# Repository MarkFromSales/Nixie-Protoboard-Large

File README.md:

# Nixie-Protoboard-Large Board
Protoboard for testing Nixie tube driving software development

I have a bunch of the new-old-stock K155ID1 chips that I found cheap on Amazon and eBay. I've been told NTE still makes the 74141 and found these links,

http://www.nteinc.com/specs/7400to7499/pdf/nte74141.pdf
http://dilp.netcomponents.com/cgi-bin/nteinc.asp?partnumber1=NTE74141

# Nixie Tube Tester Code
Learning to code for the Arduino for a Nixie tube project.
ATmega328 Driving SN74141 Nixie driver chip via pins A, B, C, & D

## Attributions and Thanks
- ATMega328 outside of Arduino Uno - https://dronebotworkshop.com/arduino-uno-atmega328/
- Multi-tasking the Arduino - https://learn.adafruit.com/multi-tasking-the-arduino-part-1?view=all

## Connections
```
ATMega328 Pin 28 (Analog 5 - I2C Clock) to MCP Pin 12
ATMega328 Pin 27 (Analog 4 - I2C Data)  to MCP Pin 13

MCP Pins #15, 16 and 17 are address selection (see below)
MCP Pin  9 to 5V
MCP Pin 10 to GND
MCP Pin 18 to 10K Resistor to 5V (reset pin, active low)
```

## MCP Addresses
```
addr 0 = A2 low,  A1 low,  A0 low  000
addr 1 = A2 low,  A1 low,  A0 high 001
addr 2 = A2 low,  A1 high, A0 low  010
addr 3 = A2 low,  A1 high, A0 high 011
addr 4 = A2 high, A1 low,  A0 low  100
addr 5 = A2 high, A1 low,  A0 high 101
addr 6 = A2 high, A1 high, A0 low  110
addr 7 = A2 high, A1 high, A0 high 111
```

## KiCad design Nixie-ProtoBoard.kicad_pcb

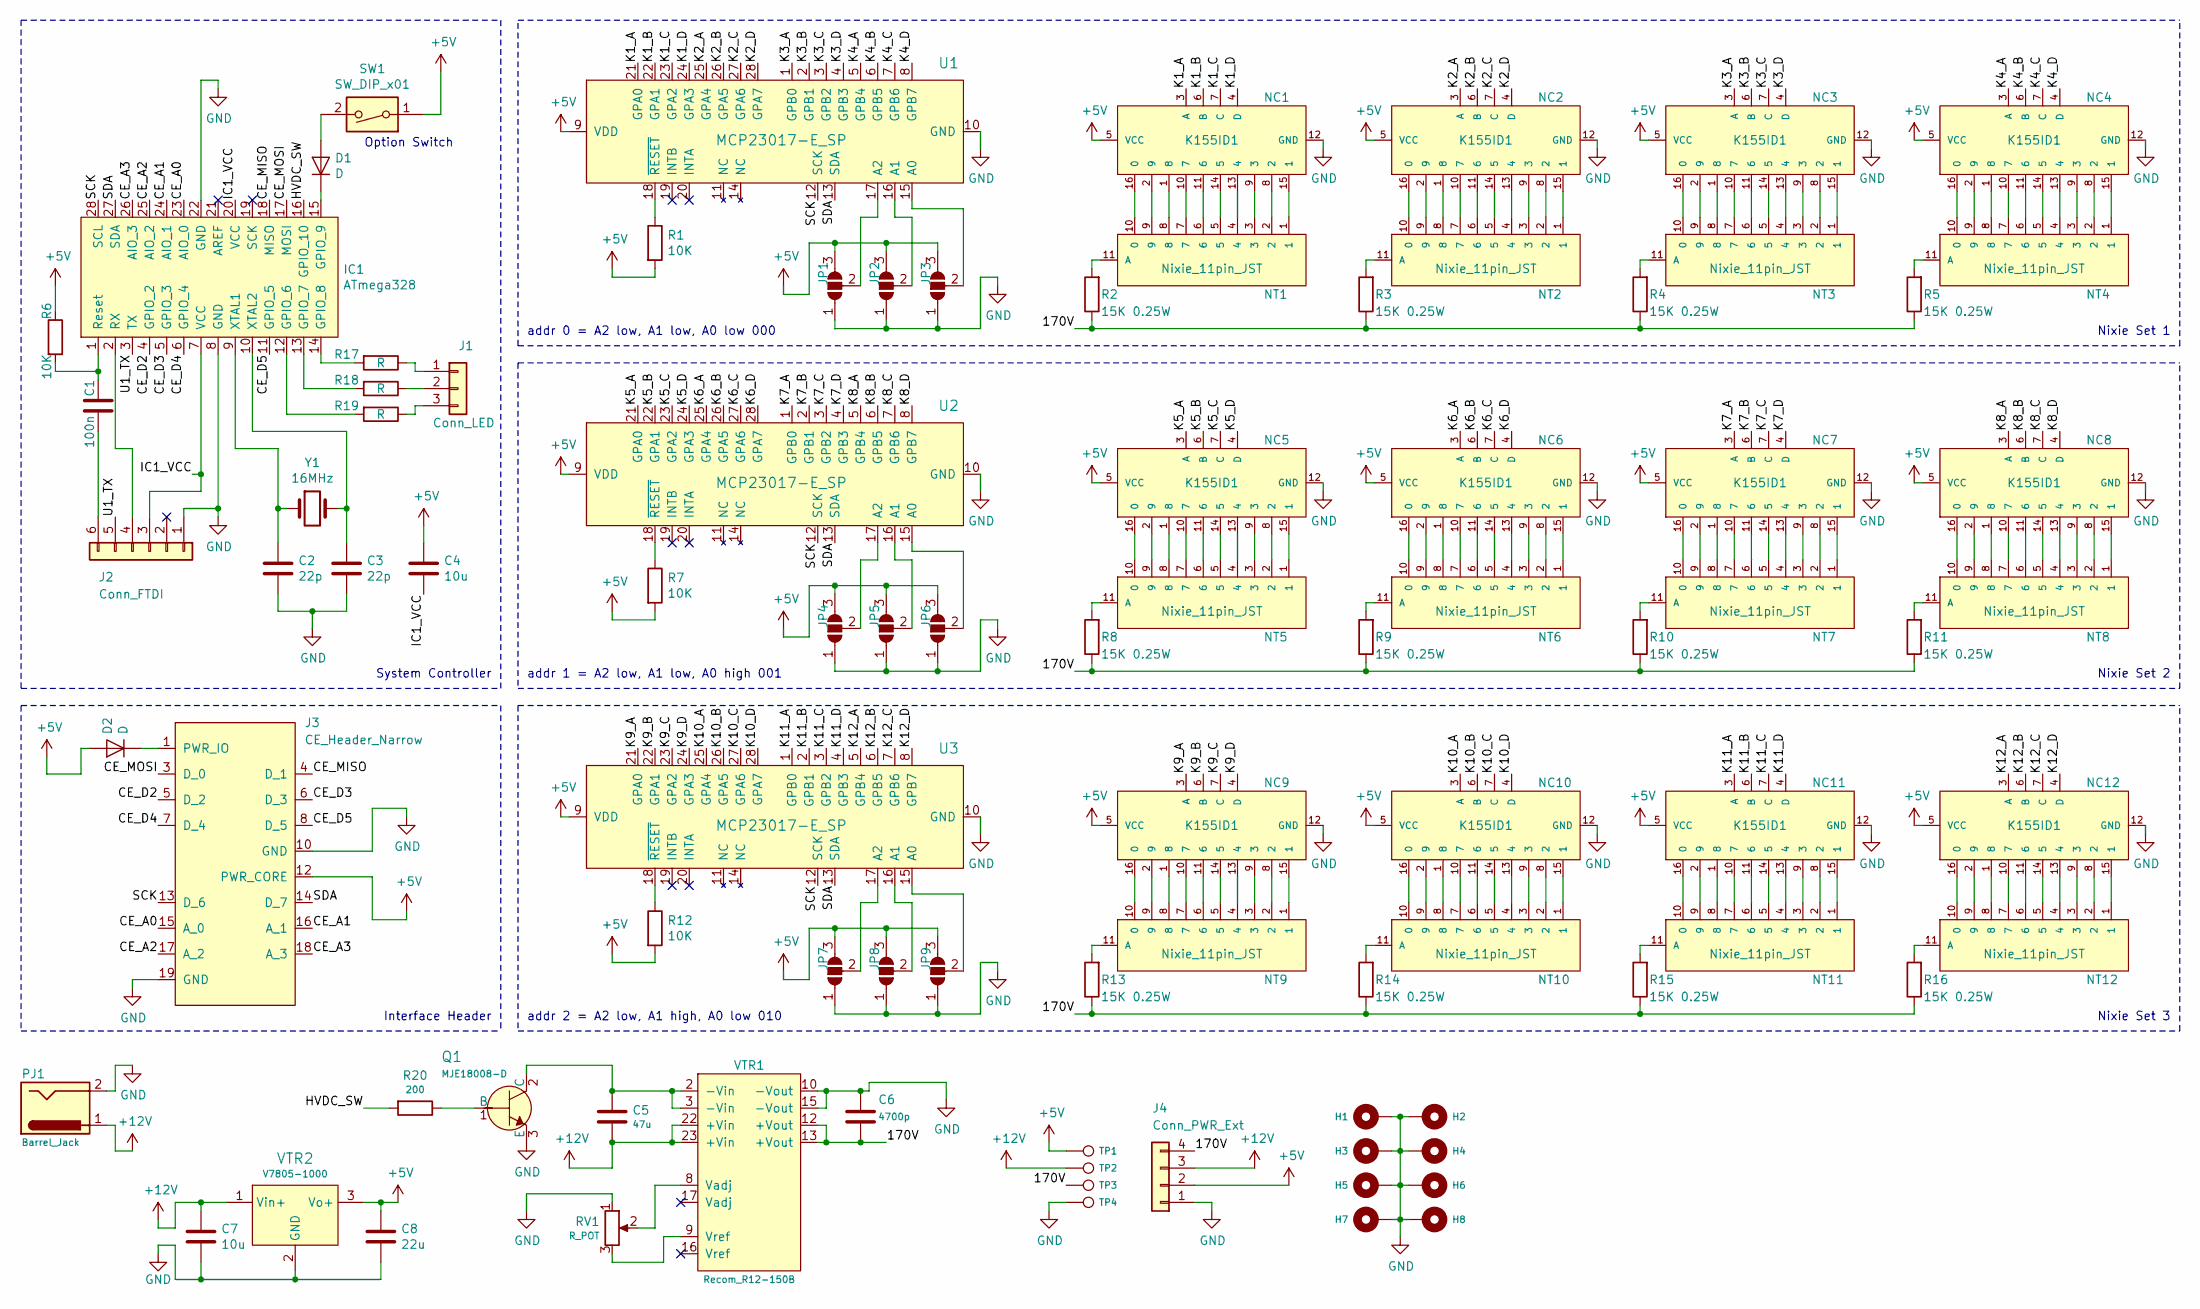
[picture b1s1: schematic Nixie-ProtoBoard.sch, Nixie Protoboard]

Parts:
C1: 100n; C_Disc_D10.5mm_W5.0mm_P7.50mm
C2, C3: 22p; C_0805_2012Metric_Pad1.15x1.40mm_HandSolder
C4, C7: 10u; C_0805_2012Metric_Pad1.15x1.40mm_HandSolder
C5: 47u; C_0805_2012Metric_Pad1.15x1.40mm_HandSolder
C6: 4700p; C_0805_2012Metric_Pad1.15x1.40mm_HandSolder
C8: 22u; CP_Radial_D5.0mm_P2.50mm
D1, D2: D; D_0805_2012Metric_Pad1.15x1.40mm_HandSolder
H1, H2, H3, H4, H5, H6, H7, H8: MountingHole_Pad; MountingHole_3.2mm_M3_Pad
IC1: ATmega328; DIP-28_W7.62mm_Socket
J1: Conn_LED; JST_XH_B03B-XH-A_1x03_P2.50mm_Vertical
J2: Conn_FTDI; PinHeader_1x06_P2.54mm_Vertical
J3: CE_Header_Narrow; PinHeader_2x10_P2.54mm_Vertical
J4: Conn_PWR_Ext; JST_VH_B4P-VH_1x04_P3.96mm_Vertical
JP1, JP2, JP3, JP4, JP5, JP6, JP7, JP8, JP9: SolderJumper_3_Open; SolderJumper-3_P1.3mm_Open_RoundedPad1.0x1.5mm_NumberLabels
NC1, NC2, NC3, NC4, NC5, NC6, NC7, NC8, NC9, NC10, NC11, NC12: K155ID1; DIP-16_W7.62mm_Socket
NT1, NT2, NT3, NT4, NT5, NT6, NT7, NT8, NT9, NT10, NT11, NT12: Nixie_11pin_JST; JST_XH_B11B-XH-A_1x11_P2.50mm_Vertical
PJ1: Barrel_Jack; BarrelJack_CUI_PJ-102AH_Horizontal
Q1: MJE18008-D; TO-220-3; MPN MJE15030G; Digi-Key_PN MJE15030GOS-ND
R1, R6, R7, R12: 10K; R_0805_2012Metric_Pad1.15x1.40mm_HandSolder
R2, R3, R4, R5, R8, R9, R10, R11, R13, R14, R15, R16: 15K 0.25W; R_0805_2012Metric_Pad1.15x1.40mm_HandSolder
R17, R18, R19: R; R_0805_2012Metric_Pad1.15x1.40mm_HandSolder
R20: 200; R_0805_2012Metric_Pad1.15x1.40mm_HandSolder
RV1: R_POT; Potentiometer_Vishay_43_Horizontal
SW1: SW_DIP_x01; PinHeader_1x02_P2.54mm_Vertical
TP1, TP2, TP3, TP4: TestPoint; TestPoint_Pad_D2.0mm
U1, U2, U3: MCP23017-E_SP; DIP-28_W7.62mm; MPN MCP23017-E/SP; Digi-Key_PN MCP23017-E/SP-ND
VTR1: Recom_R12-150B; DIP-24_W15.24mm
VTR2: V7805-1000; 3-SIP_Module_V7805-1000; MPN V7805-1000; Digi-Key_PN 102-1715-ND
Y1: 16MHz; Resonator-2Pin_W10.0mm_H5.0mm

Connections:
+5V: C4.1, C8.1, D2.2 (A), J3.12 (PWR_CORE), J4.2, JP1.3 (B), JP2.3 (B), JP3.3 (B), JP4.3 (B), JP5.3 (B), JP6.3 (B), JP7.3 (B), JP8.3 (B), JP9.3 (B), NC1.5 (VCC), NC2.5 (VCC), NC3.5 (VCC), NC4.5 (VCC), NC5.5 (VCC), NC6.5 (VCC), NC7.5 (VCC), NC8.5 (VCC), NC9.5 (VCC), NC10.5 (VCC), NC11.5 (VCC), NC12.5 (VCC), R1.2, R6.1, R7.2, R12.2, SW1.1, TP1.1, U1.9 (VDD), U2.9 (VDD), U3.9 (VDD), VTR2.3 (Vo+)
+12V: C5.2, C7.1, J4.3, PJ1.1, TP2.1, VTR1.22 (+Vin), VTR1.23 (+Vin), VTR2.1 (Vin+)
/170V: C6.2, J4.4, R2.1, R3.1, R4.1, R5.1, R8.1, R9.1, R10.1, R11.1, R13.1, R14.1, R15.1, R16.1, TP3.1, VTR1.12 (+Vout), VTR1.13 (+Vout)
/CE_A0: IC1.23 (AIO_0), J3.15 (A_0)
/CE_A1: IC1.24 (AIO_1), J3.16 (A_1)
/CE_A2: IC1.25 (AIO_2), J3.17 (A_2)
/CE_A3: IC1.26 (AIO_3), J3.18 (A_3)
/CE_D2: IC1.4 (GPIO_2), J3.5 (D_2)
/CE_D3: IC1.5 (GPIO_3), J3.6 (D_3)
/CE_D4: IC1.6 (GPIO_4), J3.7 (D_4)
/CE_D5: IC1.11 (GPIO_5), J3.8 (D_5)
/CE_MISO: IC1.18 (MISO), J3.4 (D_1)
/CE_MOSI: IC1.17 (MOSI), J3.3 (D_0)
/HVDC_SW: IC1.16 (GPIO_10), R20.2
/IC1_VCC: C4.2, IC1.7 (VCC), IC1.20 (VCC), J2.3
/K1_A: NC1.3 (A), U1.21 (GPA0)
/K1_B: NC1.6 (B), U1.22 (GPA1)
/K1_C: NC1.7 (C), U1.23 (GPA2)
/K1_D: NC1.4 (D), U1.24 (GPA3)
/K2_A: NC2.3 (A), U1.25 (GPA4)
/K2_B: NC2.6 (B), U1.26 (GPA5)
/K2_C: NC2.7 (C), U1.27 (GPA6)
/K2_D: NC2.4 (D), U1.28 (GPA7)
/K3_A: NC3.3 (A), U1.1 (GPB0)
/K3_B: NC3.6 (B), U1.2 (GPB1)
/K3_C: NC3.7 (C), U1.3 (GPB2)
/K3_D: NC3.4 (D), U1.4 (GPB3)
/K4_A: NC4.3 (A), U1.5 (GPB4)
/K4_B: NC4.6 (B), U1.6 (GPB5)
/K4_C: NC4.7 (C), U1.7 (GPB6)
/K4_D: NC4.4 (D), U1.8 (GPB7)
/K5_A: NC5.3 (A), U2.21 (GPA0)
/K5_B: NC5.6 (B), U2.22 (GPA1)
/K5_C: NC5.7 (C), U2.23 (GPA2)
/K5_D: NC5.4 (D), U2.24 (GPA3)
/K6_A: NC6.3 (A), U2.25 (GPA4)
/K6_B: NC6.6 (B), U2.26 (GPA5)
/K6_C: NC6.7 (C), U2.27 (GPA6)
/K6_D: NC6.4 (D), U2.28 (GPA7)
/K7_A: NC7.3 (A), U2.1 (GPB0)
/K7_B: NC7.6 (B), U2.2 (GPB1)
/K7_C: NC7.7 (C), U2.3 (GPB2)
/K7_D: NC7.4 (D), U2.4 (GPB3)
/K8_A: NC8.3 (A), U2.5 (GPB4)
/K8_B: NC8.6 (B), U2.6 (GPB5)
/K8_C: NC8.7 (C), U2.7 (GPB6)
/K8_D: NC8.4 (D), U2.8 (GPB7)
/K9_A: NC9.3 (A), U3.21 (GPA0)
/K9_B: NC9.6 (B), U3.22 (GPA1)
/K9_C: NC9.7 (C), U3.23 (GPA2)
/K9_D: NC9.4 (D), U3.24 (GPA3)
/K10_A: NC10.3 (A), U3.25 (GPA4)
/K10_B: NC10.6 (B), U3.26 (GPA5)
/K10_C: NC10.7 (C), U3.27 (GPA6)
/K10_D: NC10.4 (D), U3.28 (GPA7)
/K11_A: NC11.3 (A), U3.1 (GPB0)
/K11_B: NC11.6 (B), U3.2 (GPB1)
/K11_C: NC11.7 (C), U3.3 (GPB2)
/K11_D: NC11.4 (D), U3.4 (GPB3)
/K12_A: NC12.3 (A), U3.5 (GPB4)
/K12_B: NC12.6 (B), U3.6 (GPB5)
/K12_C: NC12.7 (C), U3.7 (GPB6)
/K12_D: NC12.4 (D), U3.8 (GPB7)
/SCK: IC1.28 (SCL), J3.13 (D_6), U1.12 (SCK), U2.12 (SCK), U3.12 (SCK)
/SDA: IC1.27 (SDA), J3.14 (D_7), U1.13 (SDA), U2.13 (SDA), U3.13 (SDA)
/U1_TX: IC1.3 (TX), J2.5
GND: C2.2, C3.2, C6.1, C7.2, C8.2, H1.1, H2.1, H3.1, H4.1, H5.1, H6.1, H7.1, H8.1, IC1.8 (GND), IC1.22 (GND), J2.1, J3.10 (GND), J3.19 (GND), J4.1, JP1.1 (A), JP2.1 (A), JP3.1 (A), JP4.1 (A), JP5.1 (A), JP6.1 (A), JP7.1 (A), JP8.1 (A), JP9.1 (A), NC1.12 (GND), NC2.12 (GND), NC3.12 (GND), NC4.12 (GND), NC5.12 (GND), NC6.12 (GND), NC7.12 (GND), NC8.12 (GND), NC9.12 (GND), NC10.12 (GND), NC11.12 (GND), NC12.12 (GND), PJ1.2, Q1.3 (E), RV1.1, TP4.1, U1.10 (GND), U2.10 (GND), U3.10 (GND), VTR1.10 (-Vout), VTR1.15 (-Vout), VTR2.2 (GND)
unnamed: C1.1, IC1.1 (Reset), R6.2
unnamed: C1.2, J2.6
unnamed: C2.1, IC1.9 (XTAL1), Y1.1
unnamed: C3.1, IC1.10 (XTAL2), Y1.2
unnamed: C5.1, Q1.2 (C), VTR1.2 (-Vin), VTR1.3 (-Vin)
unnamed: D1.1 (K), IC1.15 (GPIO_9)
unnamed: D1.2 (A), SW1.2
unnamed: D2.1 (K), J3.1 (PWR_IO)
unnamed: IC1.2 (RX), J2.4
unnamed: IC1.12 (GPIO_6), R19.2
unnamed: IC1.13 (GPIO_7), R18.2
unnamed: IC1.14 (GPIO_8), R17.2
unnamed: J1.1, R17.1
unnamed: J1.2, R18.1
unnamed: J1.3, R19.1
unnamed: JP1.2 (C), U1.17 (A2)
unnamed: JP2.2 (C), U1.16 (A1)
unnamed: JP3.2 (C), U1.15 (A0)
unnamed: JP4.2 (C), U2.17 (A2)
unnamed: JP5.2 (C), U2.16 (A1)
unnamed: JP6.2 (C), U2.15 (A0)
unnamed: JP7.2 (C), U3.17 (A2)
unnamed: JP8.2 (C), U3.16 (A1)
unnamed: JP9.2 (C), U3.15 (A0)
unnamed: NC1.1 (8), NT1.8
unnamed: NC1.2 (9), NT1.9
unnamed: NC1.8 (2), NT1.2
unnamed: NC1.9 (3), NT1.3
unnamed: NC1.10 (7), NT1.7
unnamed: NC1.11 (6), NT1.6
unnamed: NC1.13 (4), NT1.4
unnamed: NC1.14 (5), NT1.5
unnamed: NC1.15 (1), NT1.1
unnamed: NC1.16 (0), NT1.10 (0)
unnamed: NC2.1 (8), NT2.8
unnamed: NC2.2 (9), NT2.9
unnamed: NC2.8 (2), NT2.2
unnamed: NC2.9 (3), NT2.3
unnamed: NC2.10 (7), NT2.7
unnamed: NC2.11 (6), NT2.6
unnamed: NC2.13 (4), NT2.4
unnamed: NC2.14 (5), NT2.5
unnamed: NC2.15 (1), NT2.1
unnamed: NC2.16 (0), NT2.10 (0)
unnamed: NC3.1 (8), NT3.8
unnamed: NC3.2 (9), NT3.9
unnamed: NC3.8 (2), NT3.2
unnamed: NC3.9 (3), NT3.3
unnamed: NC3.10 (7), NT3.7
unnamed: NC3.11 (6), NT3.6
unnamed: NC3.13 (4), NT3.4
unnamed: NC3.14 (5), NT3.5
unnamed: NC3.15 (1), NT3.1
unnamed: NC3.16 (0), NT3.10 (0)
unnamed: NC4.1 (8), NT4.8
unnamed: NC4.2 (9), NT4.9
unnamed: NC4.8 (2), NT4.2
unnamed: NC4.9 (3), NT4.3
unnamed: NC4.10 (7), NT4.7
unnamed: NC4.11 (6), NT4.6
unnamed: NC4.13 (4), NT4.4
unnamed: NC4.14 (5), NT4.5
unnamed: NC4.15 (1), NT4.1
unnamed: NC4.16 (0), NT4.10 (0)
unnamed: NC5.1 (8), NT5.8
unnamed: NC5.2 (9), NT5.9
unnamed: NC5.8 (2), NT5.2
unnamed: NC5.9 (3), NT5.3
unnamed: NC5.10 (7), NT5.7
unnamed: NC5.11 (6), NT5.6
unnamed: NC5.13 (4), NT5.4
unnamed: NC5.14 (5), NT5.5
unnamed: NC5.15 (1), NT5.1
unnamed: NC5.16 (0), NT5.10 (0)
unnamed: NC6.1 (8), NT6.8
unnamed: NC6.2 (9), NT6.9
unnamed: NC6.8 (2), NT6.2
unnamed: NC6.9 (3), NT6.3
unnamed: NC6.10 (7), NT6.7
unnamed: NC6.11 (6), NT6.6
unnamed: NC6.13 (4), NT6.4
unnamed: NC6.14 (5), NT6.5
unnamed: NC6.15 (1), NT6.1
unnamed: NC6.16 (0), NT6.10 (0)
unnamed: NC7.1 (8), NT7.8
unnamed: NC7.2 (9), NT7.9
unnamed: NC7.8 (2), NT7.2
unnamed: NC7.9 (3), NT7.3
unnamed: NC7.10 (7), NT7.7
unnamed: NC7.11 (6), NT7.6
unnamed: NC7.13 (4), NT7.4
unnamed: NC7.14 (5), NT7.5
unnamed: NC7.15 (1), NT7.1
unnamed: NC7.16 (0), NT7.10 (0)
unnamed: NC8.1 (8), NT8.8
unnamed: NC8.2 (9), NT8.9
unnamed: NC8.8 (2), NT8.2
unnamed: NC8.9 (3), NT8.3
unnamed: NC8.10 (7), NT8.7
unnamed: NC8.11 (6), NT8.6
unnamed: NC8.13 (4), NT8.4
unnamed: NC8.14 (5), NT8.5
unnamed: NC8.15 (1), NT8.1
unnamed: NC8.16 (0), NT8.10 (0)
unnamed: NC9.1 (8), NT9.8
unnamed: NC9.2 (9), NT9.9
unnamed: NC9.8 (2), NT9.2
unnamed: NC9.9 (3), NT9.3
unnamed: NC9.10 (7), NT9.7
unnamed: NC9.11 (6), NT9.6
unnamed: NC9.13 (4), NT9.4
unnamed: NC9.14 (5), NT9.5
unnamed: NC9.15 (1), NT9.1
unnamed: NC9.16 (0), NT9.10 (0)
unnamed: NC10.1 (8), NT10.8
unnamed: NC10.2 (9), NT10.9
unnamed: NC10.8 (2), NT10.2
unnamed: NC10.9 (3), NT10.3
unnamed: NC10.10 (7), NT10.7
unnamed: NC10.11 (6), NT10.6
unnamed: NC10.13 (4), NT10.4
unnamed: NC10.14 (5), NT10.5
unnamed: NC10.15 (1), NT10.1
unnamed: NC10.16 (0), NT10.10 (0)
unnamed: NC11.1 (8), NT11.8
unnamed: NC11.2 (9), NT11.9
unnamed: NC11.8 (2), NT11.2
unnamed: NC11.9 (3), NT11.3
unnamed: NC11.10 (7), NT11.7
unnamed: NC11.11 (6), NT11.6
unnamed: NC11.13 (4), NT11.4
unnamed: NC11.14 (5), NT11.5
unnamed: NC11.15 (1), NT11.1
unnamed: NC11.16 (0), NT11.10 (0)
unnamed: NC12.1 (8), NT12.8
unnamed: NC12.2 (9), NT12.9
unnamed: NC12.8 (2), NT12.2
unnamed: NC12.9 (3), NT12.3
unnamed: NC12.10 (7), NT12.7
unnamed: NC12.11 (6), NT12.6
unnamed: NC12.13 (4), NT12.4
unnamed: NC12.14 (5), NT12.5
unnamed: NC12.15 (1), NT12.1
unnamed: NC12.16 (0), NT12.10 (0)
unnamed: NT1.11 (A), R2.2
unnamed: NT2.11 (A), R3.2
unnamed: NT3.11 (A), R4.2
unnamed: NT4.11 (A), R5.2
unnamed: NT5.11 (A), R8.2
unnamed: NT6.11 (A), R9.2
unnamed: NT7.11 (A), R10.2
unnamed: NT8.11 (A), R11.2
unnamed: NT9.11 (A), R13.2
unnamed: NT10.11 (A), R14.2
unnamed: NT11.11 (A), R15.2
unnamed: NT12.11 (A), R16.2
unnamed: Q1.1 (B), R20.1
unnamed: R1.1, U1.18 (~RESET)
unnamed: R7.1, U2.18 (~RESET)
unnamed: R12.1, U3.18 (~RESET)
unnamed: RV1.2, VTR1.8 (Vadj)
unnamed: RV1.3, VTR1.9 (Vref)

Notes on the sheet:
Nixie Set 1
Nixie Set 2
System Controller
Option Switch
Nixie Set 3
addr 0 = A2 low, A1 low, A0 low 000
addr 1 = A2 low, A1 low, A0 high 001
addr 2 = A2 low, A1 high, A0 low 010
Interface Header

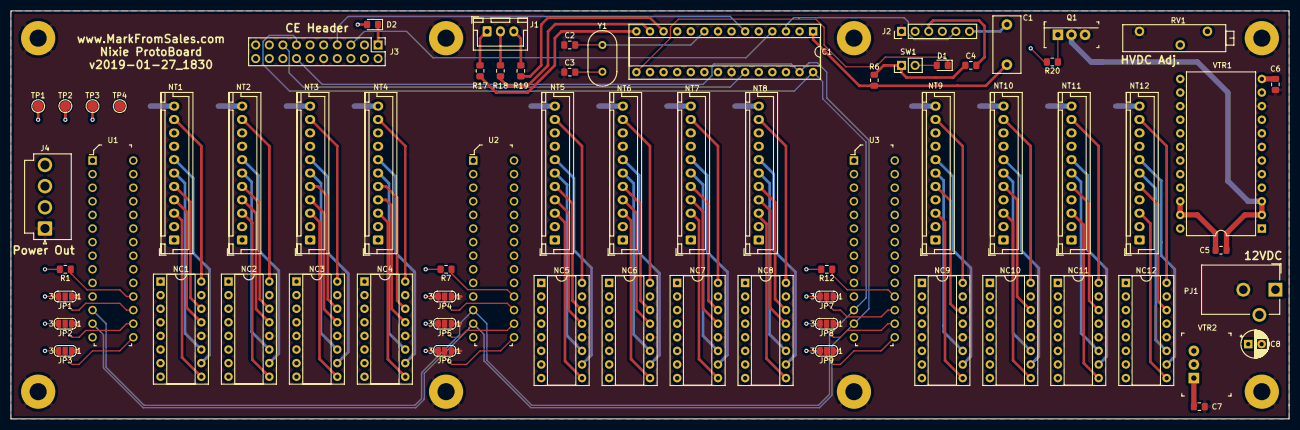
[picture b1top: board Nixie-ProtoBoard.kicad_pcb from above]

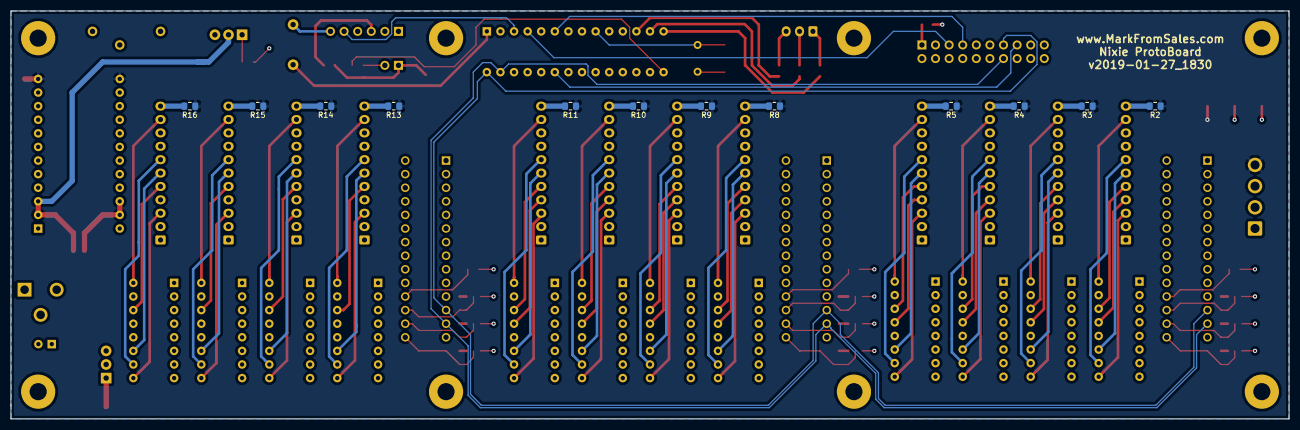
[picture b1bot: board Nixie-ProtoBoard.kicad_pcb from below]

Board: 4 copper layers, 238.8 x 76.2 mm, 90 parts (12 on the bottom side), 229 nets.

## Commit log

2019-02-02 Initial Upload
2019-02-02 Arduino code
2019-02-10 Minor updates
2019-02-13 Updated structure
